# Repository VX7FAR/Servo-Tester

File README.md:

# SERVO TESTER

A servo tester is basically a device someone can use to check whether their servo motors work or not and this can be very essential as it can help you to check your servo motors before having to write new code just to run a single servo.
Most of the servo need 1ms to 2ms pulse so that it moves from 0 to 180 degrees respectively.

Here is a normal view of servo tester:

Exploded View:

## WORKING / SCHEMATIC

The main component here is Arduino Nano I chose this specially because this servo tester also has a 0.91 inch display module.
The display shows stats like speed, angle, mode, etc.
It also feature a potentiometer to control different things based on the mode selected
It also has two buttons one is for resetting to original position and other is for switching between sweep and manual mode.

### The servo tester has 4 modes which are:
- Manual Mode : As the name suggests here you control the servo manually by using the potentiometer. In this potentiometer controls the position of servo.
- Sweep : In this the servo moves from the minimum position to maximum position it can attain between 1ms to 2ms pulses which in most cases is between 0 to 180 degrees. In this the potentiometer controls the speed of sweep of servo.
- Calibration : I added this mode because if someone chose to have a different kind of potentiometer then the readings may become incorrect, which is why in calibration mode you can make your servo tester adapt to your potentiometer. In this the potentiometer is used for setting the maximum and minimum position.
It can be selected by pressing the two buttons simultaneously.
- RESET : In this the servo moves to the initial position and stays like that.

## Bill of Materials

| Component | Quantity | 
|-----------|----------|
| Arduino Nano | 1 |
| Arduino Data Cable | 1 |
| 0.91" OLED Display Module | 1 |
| Push Button | 2 |
| Toggle Switch | 1 |
| PCB | 1 |
| Male connector pins | 11 |
| Top enclosure | 1 |
| Middle Enclosure | 1 |
| Bottom Panel | 1 |
| 6-12V DC Power Source | 1 |
| Servo Motor (SG90) | 1 |
| 4x1.5mm magnets | 2 |
| Diodes | 2 |

## Wiring / Schematic
An overview of what the PCB is like.

Circuit:

PCB:

PCB 3D Model:

## Things to keep in mind when using the repository:
- The CAD folder contains CAD model for each part individually as well as step and f3d original files.
- The firmware was made using platformIO which is a vs code extension so you will have to load the directory where platform.ini file is. If you are using arduino IDE then you can directly copy the code `from src/main.cpp` and header is in `include/animation.h`.
- The libraries are mainly for controlling the display and they are `Adafruit_SSD1306.h` and `Adafruit_GFX.h`.
- `PCB` folder contains everything related to PCB like gerber file (`PCB-gerber.zip`), kicad files and also the 3D model of PCB (`servo tester.step`).
- `assets` folder contains things that are not really important for making the project but I kept them for having a bit easy while working and writing the README. You can freely ignore that folder if you want to.

## Things to keep in mind when using the project:
- To run the servos you will have to use an external power source which will be connected on top left of the PCB by two connector pins
- When running the servo make sure to connect the servo then power them up as there is a direct connection between ground to vcc of servo power source

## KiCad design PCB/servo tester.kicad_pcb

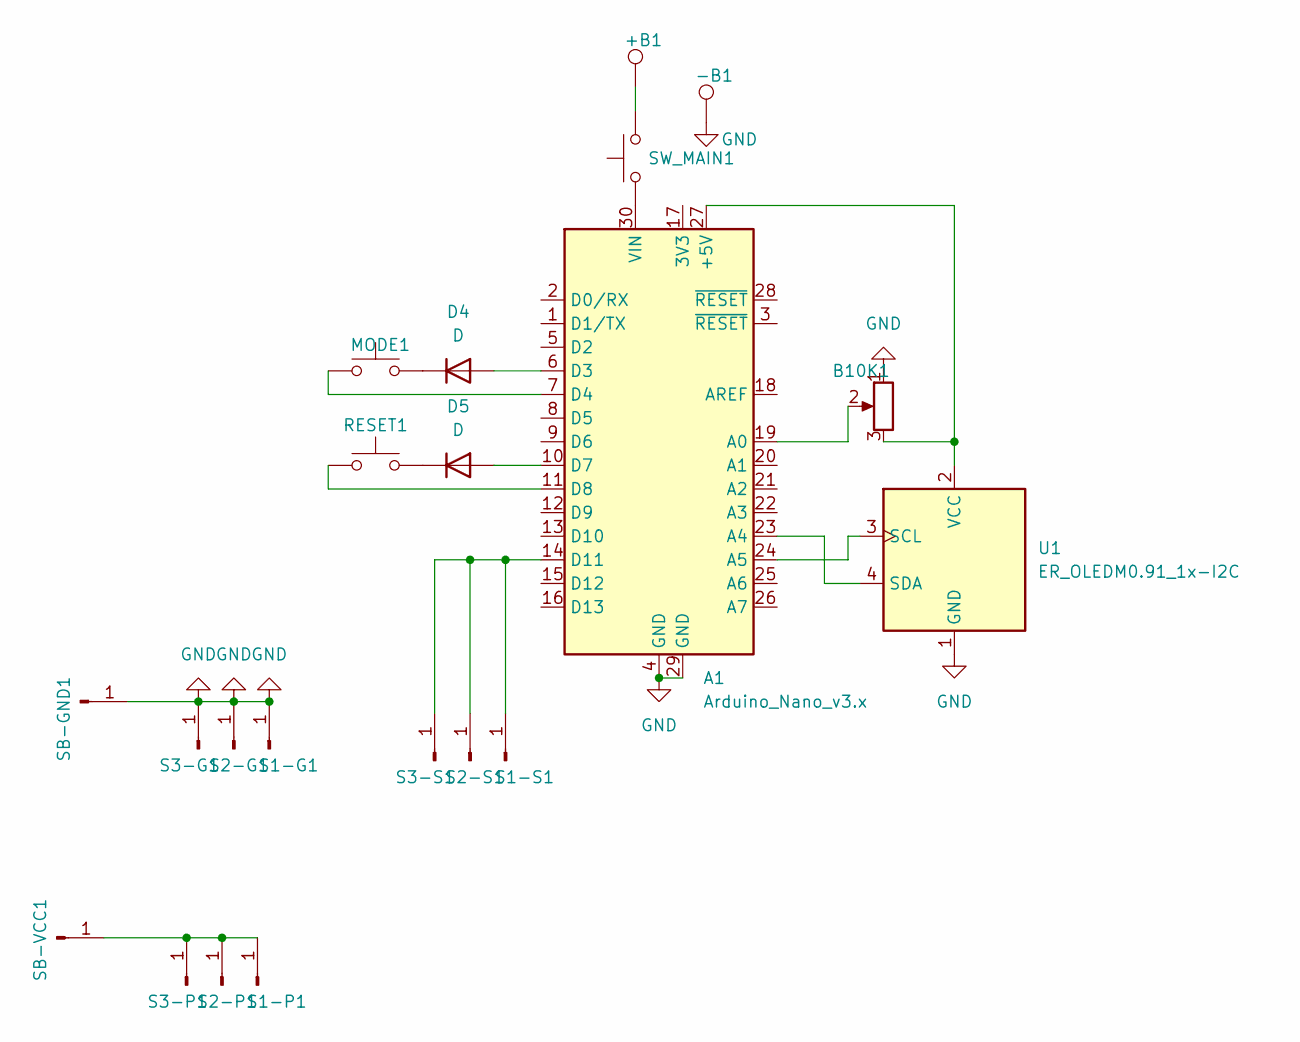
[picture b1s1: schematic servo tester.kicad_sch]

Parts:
+B1: TestPoint; SolderWire-0.5sqmm_1x01_D0.9mm_OD2.1mm
-B1: TestPoint; SolderWire-0.5sqmm_1x01_D0.9mm_OD2.1mm
A1: Arduino_Nano_v3.x; Arduino_Nano
B10K1: R_Potentiometer; Potentiometer_Bourns_3386C_Horizontal
D4, D5: D; D_A-405_P10.16mm_Horizontal
MODE1: SW_Push; SW_PUSH_6mm
RESET1: SW_Push; SW_PUSH_6mm
S1-G1, S1-P1, S1-S1, S2-G1, S2-P1, S2-S1, S3-G1, S3-P1, S3-S1: Conn_01x01_Pin; PinHeader_1x01_P2.54mm_Horizontal
SB-GND1: Conn_01x01_Pin; PinHeader_1x01_P2.54mm_Horizontal
SB-VCC1: Conn_01x01_Pin; PinHeader_1x01_P2.54mm_Horizontal
SW_MAIN1: SW_Push; SW_DIP_SPSTx01_Slide_9.78x4.72mm_W7.62mm_P2.54mm
U1: ER_OLEDM0.91_1x-I2C

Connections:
GND: -B1.1 (1_1), A1.4 (GND), A1.29 (GND), B10K1.1, S1-G1.1 (Pin_1_1), S2-G1.1 (Pin_1_1), S3-G1.1 (Pin_1_1), SB-GND1.1 (Pin_1_1), U1.1 (GND)
unnamed: +B1.1 (1_1), SW_MAIN1.2
unnamed: A1.27 (+5V), B10K1.3, U1.2 (VCC)
unnamed: A1.19 (A0), B10K1.2
unnamed: A1.23 (A4), U1.4 (SDA)
unnamed: A1.24 (A5), U1.3 (SCL)
unnamed: A1.6 (D3), D4.2 (A)
unnamed: A1.7 (D4), MODE1.1
unnamed: A1.10 (D7), D5.2 (A)
unnamed: A1.11 (D8), RESET1.1
unnamed: A1.14 (D11), S1-S1.1 (Pin_1_1), S2-S1.1 (Pin_1_1), S3-S1.1 (Pin_1_1)
unnamed: A1.30 (VIN), SW_MAIN1.1
unnamed: D4.1 (K), MODE1.2
unnamed: D5.1 (K), RESET1.2
unnamed: S1-P1.1 (Pin_1_1), S2-P1.1 (Pin_1_1), S3-P1.1 (Pin_1_1), SB-VCC1.1 (Pin_1_1)

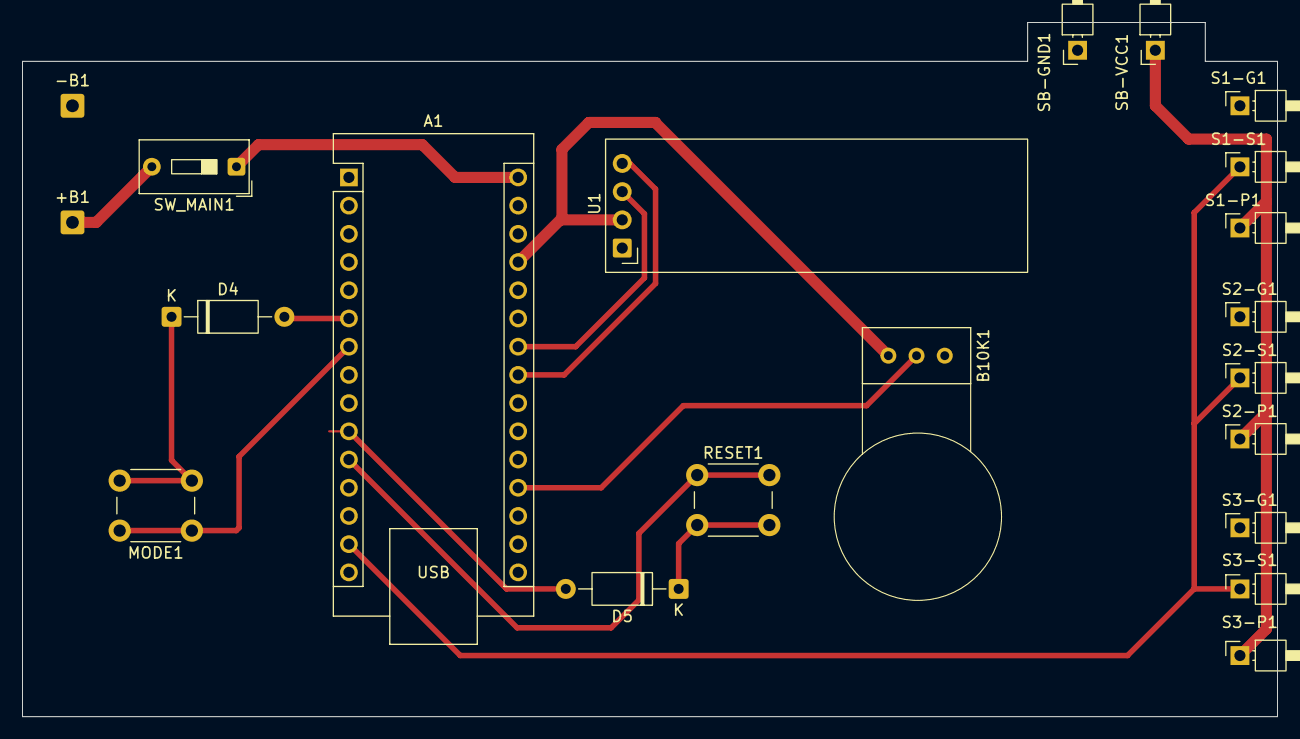
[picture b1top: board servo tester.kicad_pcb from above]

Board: 2 copper layers, 113.0 x 62.5 mm, 21 parts (0 on the bottom side), 15 nets.
